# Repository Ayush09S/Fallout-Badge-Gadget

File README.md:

# Ayush's Fallout Badge Gadget
# Context
This project was created during Hack Club's 2026 Fallout Hackathon. It will be distributed to our friends before we leave, and is being paid for by the coupon provided to us from JLCPCB with an EasyEda Account. This was created on Day 2 of Fallout. 

# Design
This PCB design features multiple of my favorite hobbies and shows that I've watched. 

Shows include:
- The Amazing Digital Circus
- How To Train Your Dragon
- Hamilton
- Avatar The Last Airbender (NOT THE BLUE PEOPLE)
Hobbies include:
- Taekwondo (The picture is just a martial art)
- Robotics
- Hockey

I've also added some Hack Club assets, such as Soup, the Fallout logo and the Hack Club Flag.

The PCB can also activate LEDs that turn on through a switch. It is important to note that this PCB is designed to be without PCBA (without Assembly) and have components hand soldered.

# Screenshots
## Schematic

## PCB

# Special Thanks
Hack Club! Thank you for running Fallout and all the other incredible Hack Club events.
My Team! Lina and Kade are awesome and I can't wait to work with them for the rest of the event.
Thanks to Lina for reviewing my project too! And bakathefish!

# Comment
My Slack is 09s.ayush (this is for verification)

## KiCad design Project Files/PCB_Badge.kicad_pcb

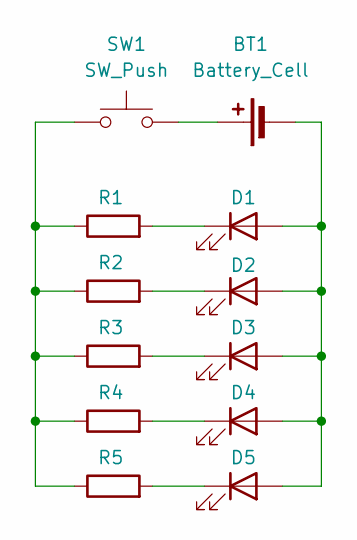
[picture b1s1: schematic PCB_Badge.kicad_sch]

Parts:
BT1: Battery_Cell; BatteryHolder_Keystone_3034_1x20mm
D1, D2, D3, D4, D5: LED; LED_D5.0mm
R1, R2, R3, R4, R5: R; R_Axial_DIN0207_L6.3mm_D2.5mm_P7.62mm_Horizontal
SW1: SW_Push; SW_PUSH_6mm

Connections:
unnamed: BT1.1 (+), SW1.2
unnamed: BT1.2 (-), D1.2 (A), D2.2 (A), D3.2 (A), D4.2 (A), D5.2 (A)
unnamed: D1.1 (K), R1.2
unnamed: D2.1 (K), R2.2
unnamed: D3.1 (K), R3.2
unnamed: D4.1 (K), R4.2
unnamed: D5.1 (K), R5.2
unnamed: R1.1, R2.1, R3.1, R4.1, R5.1, SW1.1

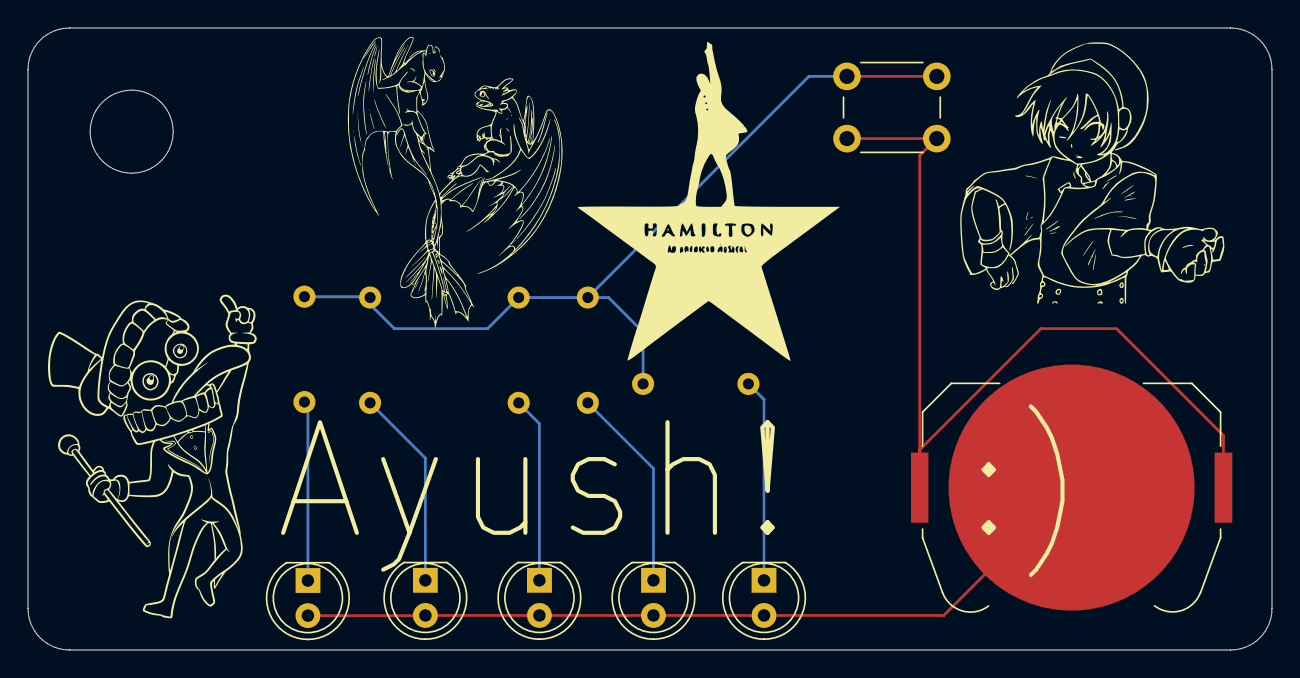
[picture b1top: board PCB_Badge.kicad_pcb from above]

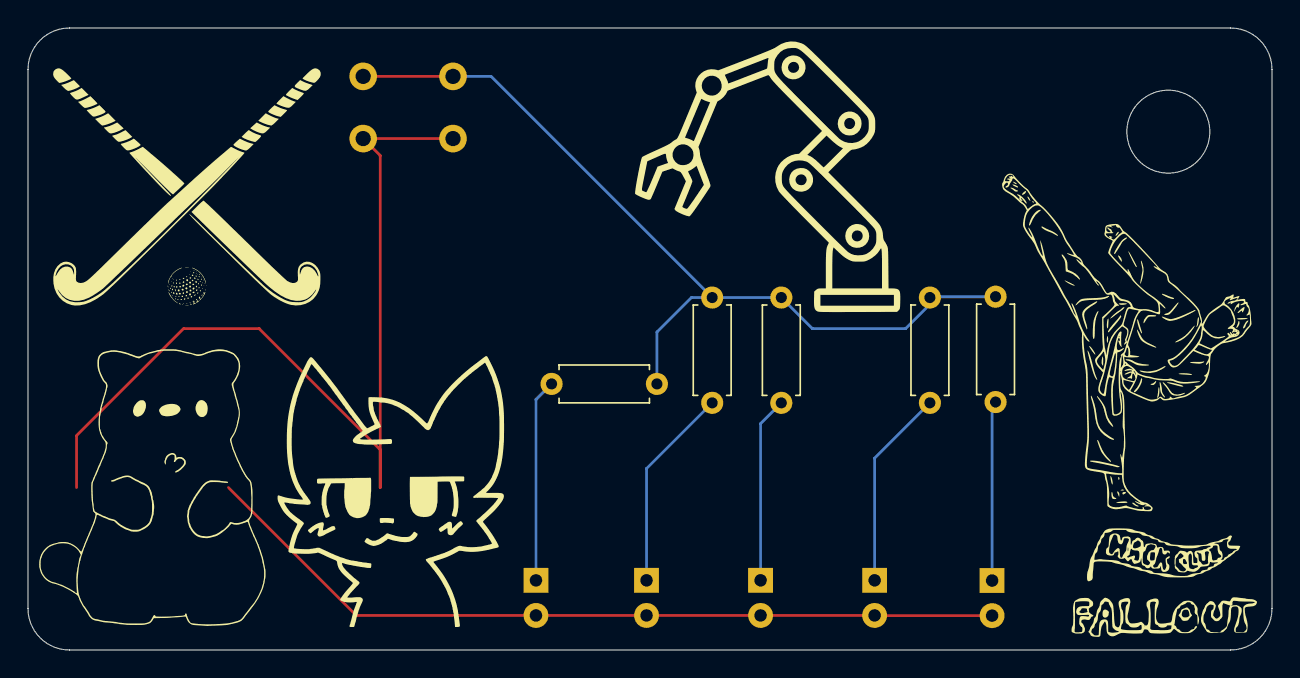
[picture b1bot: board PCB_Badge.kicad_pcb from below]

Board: 2 copper layers, 90.0 x 45.0 mm, 12 parts (5 on the bottom side), 8 nets.
